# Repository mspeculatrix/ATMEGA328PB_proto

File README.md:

# ATMEGA328PB breakout & prototyping board

This is a breakout/prototyping board for the ATMEGA328PB microcontroller which comes in the TQFP-32 format. It allows programming of the chip and breaks out all the pins to standard DuPont headers for project prototyping. My plan is to mount this PCB on a baseboard alongside a breadboard.

The microcontroller chip is placed in a TQFP-32 adapter, such as [this one](https://www.ebay.com/itm/1Pcs-TQFP32-QFP32-TO-DIP32-28-IC-Programmer-Adapter-Chip-Test-Socket-Pitch-Black/173689092477?ssPageName=STRK%3AMEBIDX%3AIT&_trksid=p2057872.m2749.l2649). These come with carrier boards to make the adapter fit standard DIP footprints. But my board doesn't use this - it just uses the main adapter itself which I have soldered into my PCB.

The pins for the four ports, B, C, D and E are gathered together logically (whereas they are somewhat scattered around on the microcontroller chip pinout itself).

### Features
* The AVCC pin is connected to VCC using a low-pass filter - ie, via a 10µH inductor with a 0.1µF capacitor to GND. This is Atmel's recommended setup which you want to use the analogue features of the microcontroller but don't want to go to the trouble of providing a separate analogue supply.
* There's a standard 6-pin header to connect an ISP programmer auch as the ATMEL-ICE.
* The ~RESET pin (PC6) has a pullup resistor and a tactile button to reset the microcontroller.
* The standard I2C pins (PC4, PC5) both have two additional pins for easy use of more than one I2C device. The additional pins are accompanied by +5V and GND pins. Onboard 10kΩ pullup resistors can be selected or deselected using jumpers.
* Female headers allow the use of an external crystal. This can be selected or deselected using jumpers. Onboard 22pF capacitors are connected between each leg of the crystal and GND.
* The standard UART pins – RX (PD0) and TX (PD1) have additional pins. These are in a row of six pins, including a GND connection, designed to match the normal order of connections on an FTDI USB-serial cable. Two of the other pins - RTS and CTS - are connected to two more pins. You can then use short female-female jumper cables to connect RTS and DTS to the GPIO pins of your choice.
* Finally, there are three lots of 4-pin connectors all tied to GND. Marked as 'test points', these are for the easy attachment of the GND clip for oscilloscope probes.
* There's an on-off slide switch for power. It is possible, however, that the board will be back-powered through any signals applied to the GPIO pins. Other than buffering every pin, I don't see any way to avoid this, so it's just something to watch out for.

### Notes
* The power connector is a simple two-pin header. NO REVERSE POLARITY PROTECTION IS PROVIDED. Nor is there any over-voltage protection.
* The board is intended to be powered by 5V, although it might work on 3.3V (I haven't thought that through).

### Progress
I've received the first batch of Rev 1.0 boards and have made up one, hand-soldered board. And, so far, it has worked flawlessly.

***
### Resources
* [Background to the project](https://mansfield-devine.com/speculatrix/2019/07/atmega328pb-breakout-and-prototyping-board/)

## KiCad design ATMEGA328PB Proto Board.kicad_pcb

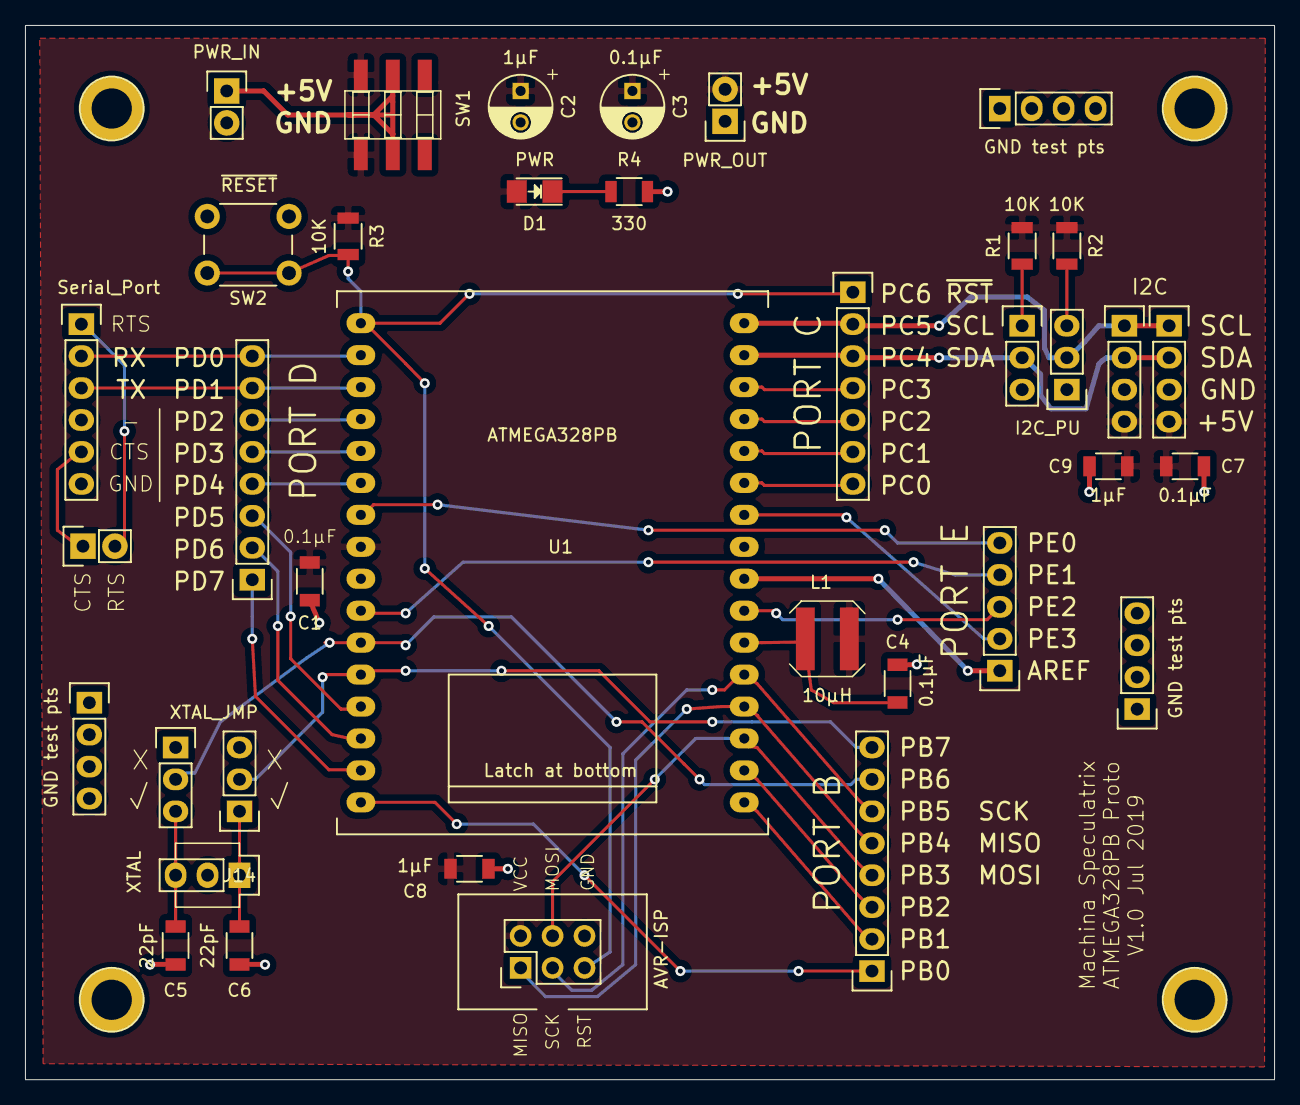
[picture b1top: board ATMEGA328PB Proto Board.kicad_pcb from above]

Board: 2 copper layers, 99.3 x 83.8 mm, 37 parts (0 on the bottom side), 39 nets.

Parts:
C1, C4, C7: 0.1µF; C_1206
C2: 1µF; C_Radial_D5_L6_P2.5
C3: 0.1µF; C_Radial_D5_L6_P2.5
C5, C6: 22pF; C_1206
C8, C9: 1µF; C_1206
CONN1: AVR-ISP; AVR_ISP_HE10_2x3
D1: PWR; LED_1206
J1: PWR_IN; Pin_Header_Straight_1x02
J2: PORT B; Pin_Header_Straight_1x08
J3: PORT C; Pin_Header_Straight_1x07
J4: PORT D; Pin_Header_Straight_1x08
J5: PORT E; Pin_Header_Straight_1x05
J6, J7: I2C; Pin_Header_Straight_1x04
J9: I2C_PU; Pin_Header_Straight_1x03
J10: SCL_PU; Pin_Header_Straight_1x03
J11: PWR_OUT; Pin_Header_Straight_1x02
J12: XTAL_JMP; Pin_Header_Straight_1x03
J13: XTAL; Pin_Header_Straight_1x03
J14: XTAL2_JMP; Pin_Header_Straight_1x03
J15, J16, J19: GND test pts; Pin_Header_Straight_1x04
J17: Serial_Port; Pin_Header_Straight_1x06
J18: RTS-CTS; Pin_Header_Straight_1x02
L1: 10µH; Inductor_Bourns-SRN5020
R1, R2, R3: 10K; R_1206
R4: 330; R_1206
SW1: SW_DPDT; SW_SMD_DPDT
SW2: ~RESET; SW_PUSH_6mm
U1: ATMEGA328PB; DIP-32_TQFP_ZIF

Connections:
/AVCC: C4.1, L1.2, U1.18
/CTS: J17.5, J18.1
/PB0: J2.1, U1.12
/PB1: J2.2, U1.13
/PB2: J2.3, U1.14
/PB6: J2.7, J12.2, U1.7
/PB7: J2.8, J14.2, U1.8
/PC0: J3.7, U1.23
/PC1: J3.6, U1.24
/PC2: J3.5, U1.25
/PC3: J3.4, U1.26
/PD2: J4.6, U1.32
/PD3: J4.5, U1.1
/PD4: J4.4, U1.2
/PD5: J4.3, U1.9
/PD6: J4.2, U1.10
/PD7: J4.1, U1.11
/PE0: J5.5, U1.3
/PE1: J5.4, U1.6
/PE2: J5.3, U1.19
/PE3: J5.2, U1.22
/RTS: J17.1, J18.2
AREF: J5.1, U1.20
GND: C1.2, C2.2, C3.2, C4.2, C5.2, C6.2, C7.2, C8.2, C9.2, CONN1.6, J1.2, J6.3, J7.3, J11.1, J15.1, J15.2, J15.3, J15.4, J16.1, J16.2, J16.3, J16.4, J17.6, J19.1, J19.2, J19.3, J19.4, R4.2, SW2.2, U1.5, U1.21
unnamed: C5.1, J12.3, J13.3
unnamed: C6.1, J13.1, J14.1
unnamed: D1.1, R4.1
unnamed: J1.1, SW1.2, SW1.5
unnamed: J9.1, R1.2
unnamed: J10.3, R2.2
PB3_MOSI: CONN1.4, J2.4, U1.15
PB4_MISO: CONN1.1, J2.5, U1.16
PB5_SCK: CONN1.3, J2.6, U1.17
PC4_SDA: J3.3, J6.2, J7.2, J9.2, U1.27
PC5_SCL: J3.2, J6.1, J7.1, J10.2, U1.28
PC6_~RST: CONN1.5, J3.1, R3.2, SW2.1, U1.29
PD0_RX: J4.8, J17.2, U1.30
PD1_TX: J4.7, J17.3, U1.31
VCC: C1.1, C2.1, C3.1, C7.1, C8.1, C9.1, CONN1.2, D1.2, J6.4, J7.4, J11.2, L1.1, R1.1, R2.1, R3.1, SW1.1, SW1.4, U1.4
